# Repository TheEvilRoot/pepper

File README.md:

# pepper

Simple breakout board for E-Paper display with EPS32S3 MCU

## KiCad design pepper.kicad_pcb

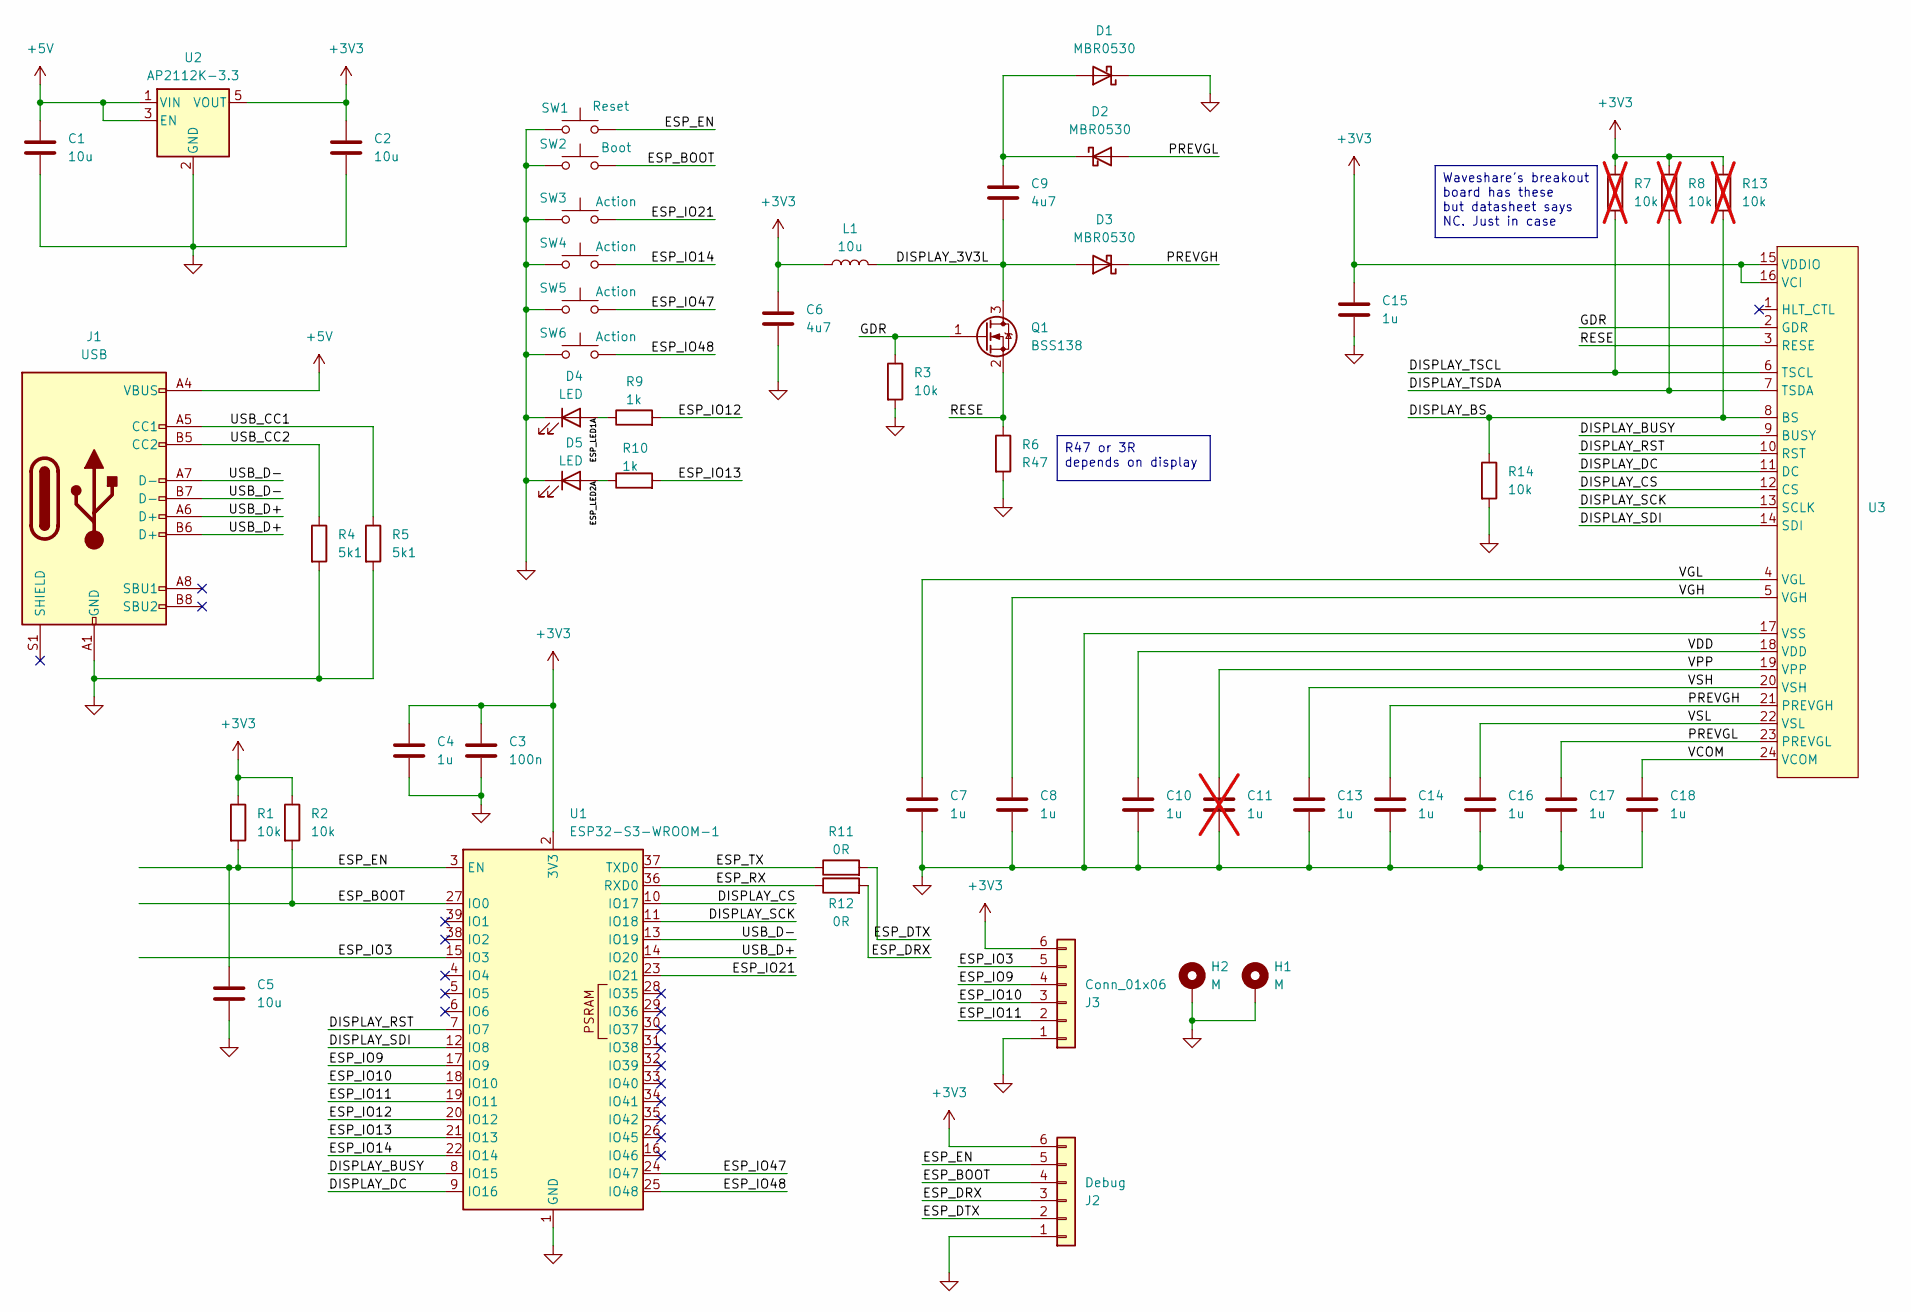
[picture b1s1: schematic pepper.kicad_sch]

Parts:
C1, C2: 10u; C_0805_2012Metric
C3: 100n; C_0603_1608Metric
C4, C7, C8, C10, C13, C14, C15, C16, C17, C18: 1u; C_0603_1608Metric
C5: 10u; C_0603_1608Metric
C6, C9: 4u7; C_0603_1608Metric
C11: 1u; C_0603_1608Metric; not fitted
D1, D2, D3: MBR0530; D_SOD-123
D4, D5: LED; LED_0603_1608Metric
H1, H2: M; MountingHole_2.2mm_M2_DIN965_Pad
J1: USB; USB_C_Receptacle_HRO_TYPE-C-31-M-12
J2: Debug; PinHeader_1x06_P2.54mm_Horizontal
J3: Conn_01x06; PinHeader_1x06_P2.54mm_Horizontal
L1: 10u; IND_CSAB0420-2R2M
Q1: BSS138; SOT-23
R1, R2, R3, R14: 10k; R_0603_1608Metric
R4, R5: 5k1; R_0603_1608Metric
R6: R47; R_0603_1608Metric
R7, R8, R13: 10k; R_0603_1608Metric; not fitted
R9, R10: 1k; R_0603_1608Metric
R11, R12: 0R; R_0603_1608Metric
SW1: Reset; SW_SPST_B3U-1000P
SW2: Boot; SW_SPST_B3U-1000P
SW3, SW4, SW5, SW6: Action; SW_SPST_TL3342
U1: ESP32-S3-WROOM-1
U2: AP2112K-3.3; SOT-23-5
U3: Hirose_FH12-24S-0.5SH_1x24-1MP_P0.50mm_Horizontal

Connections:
+3V3: C2.1, C3.1, C4.1, C6.2, C15.2, J2.6, J3.6, L1.1, R1.1, R2.1, R7.1, R8.1, R13.1, U1.2 (3V3), U2.5 (VOUT), U3.15 (VDDIO), U3.16 (VCI)
+5V: C1.1, J1.A4 (VBUS), J1.A9 (VBUS), J1.B4 (VBUS), J1.B9 (VBUS), U2.1 (VIN), U2.3 (EN)
/DISPLAY_3V3L: C9.1, D3.2 (A), L1.2, Q1.3 (D)
/DISPLAY_BS: R13.2, R14.1, U3.8 (BS)
/DISPLAY_BUSY: U1.8 (IO15), U3.9 (BUSY)
/DISPLAY_CS: U1.10 (IO17), U3.12 (CS)
/DISPLAY_DC: U1.9 (IO16), U3.11 (DC)
/DISPLAY_RST: U1.7 (IO7), U3.10 (RST)
/DISPLAY_SCK: U1.11 (IO18), U3.13 (SCLK)
/DISPLAY_SDI: U1.12 (IO8), U3.14 (SDI)
/DISPLAY_TSCL: R7.2, U3.6 (TSCL)
/DISPLAY_TSDA: R8.2, U3.7 (TSDA)
/ESP_BOOT: J2.4, R2.2, SW2.2, U1.27 (IO0)
/ESP_DRX: J2.3, R12.2
/ESP_DTX: J2.2, R11.2
/ESP_EN: C5.1, J2.5, R1.2, SW1.2, U1.3 (EN)
/ESP_IO3: J3.5, U1.15 (IO3)
/ESP_IO9: J3.4, U1.17 (IO9)
/ESP_IO10: J3.3, U1.18 (IO10)
/ESP_IO11: J3.2, U1.19 (IO11)
/ESP_IO12: R9.2, U1.20 (IO12)
/ESP_IO13: R10.2, U1.21 (IO13)
/ESP_IO14: SW4.2, U1.22 (IO14)
/ESP_IO21: SW3.2, U1.23 (IO21)
/ESP_IO47: SW5.2, U1.24 (IO47)
/ESP_IO48: SW6.2, U1.25 (IO48)
/ESP_LED1A: D4.2 (A), R9.1
/ESP_LED2A: D5.2 (A), R10.1
/ESP_RX: R12.1, U1.36 (RXD0)
/ESP_TX: R11.1, U1.37 (TXD0)
/GDR: Q1.1 (G), R3.1, U3.2 (GDR)
/PREVGH: C14.2, D3.1 (K), U3.21 (PREVGH)
/PREVGL: C17.2, D2.2 (A), U3.23 (PREVGL)
/RESE: Q1.2 (S), R6.1, U3.3 (RESE)
/USB_CC1: J1.A5 (CC1), R5.1
/USB_CC2: J1.B5 (CC2), R4.1
/USB_D+: J1.A6 (D+), J1.B6 (D+), U1.14 (IO20)
/USB_D-: J1.A7 (D-), J1.B7 (D-), U1.13 (IO19)
/VCOM: C18.2, U3.24 (VCOM)
/VDD: C10.2, U3.18 (VDD)
/VGH: C8.2, U3.5 (VGH)
/VGL: C7.2, U3.4 (VGL)
/VPP: C11.2, U3.19 (VPP)
/VSH: C13.2, U3.20 (VSH)
/VSL: C16.2, U3.22 (VSL)
GND: C1.2, C2.2, C3.2, C4.2, C5.2, C6.1, C7.1, C8.1, C10.1, C11.1, C13.1, C14.1, C15.1, C16.1, C17.1, C18.1, D1.1 (K), D4.1 (K), D5.1 (K), H1.1, H2.1, J1.A1 (GND), J1.A12 (GND), J1.B1 (GND), J1.B12 (GND), J2.1, J3.1, R3.2, R4.2, R5.2, R6.2, R14.2, SW1.1, SW2.1, SW3.1, SW4.1, SW5.1, SW6.1, U1.1 (GND), U1.40 (GND), U1.41 (GND), U2.2 (GND), U3.17 (VSS)
unnamed: C9.2, D1.2 (A), D2.1 (K)

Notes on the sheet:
R47 or 3R depends on display
Waveshare's breakout board has these but datasheet says NC. Just in case

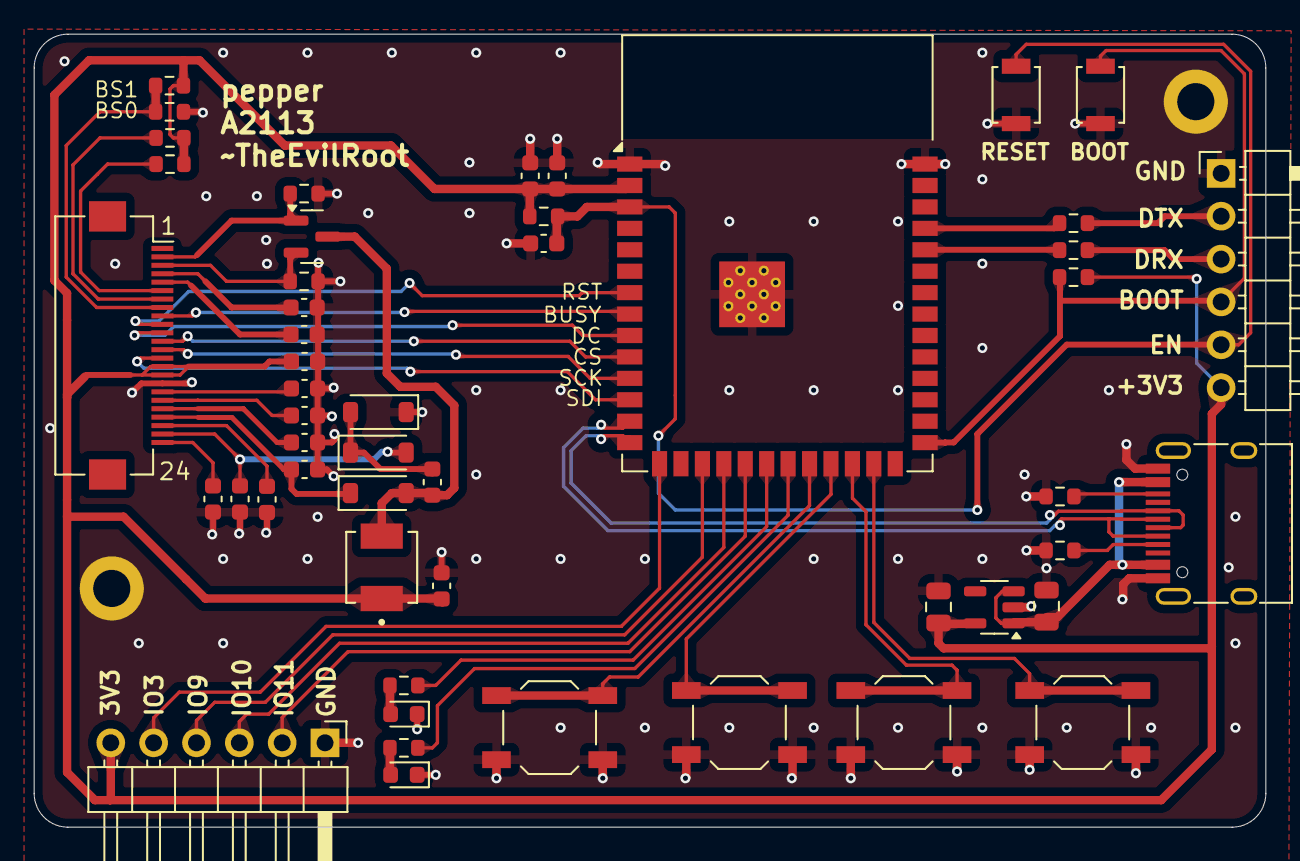
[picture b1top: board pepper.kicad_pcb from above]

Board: 2 copper layers, 73.0 x 47.0 mm, 52 parts (0 on the bottom side), 47 nets.

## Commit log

2025-02-07 Initial
2025-02-07 Add picture
2025-02-09 Redesign. Bottom control panel
2025-02-09 4 layer board. Battery charger
2025-03-01 Simple order 1
2025-03-04 Update image
